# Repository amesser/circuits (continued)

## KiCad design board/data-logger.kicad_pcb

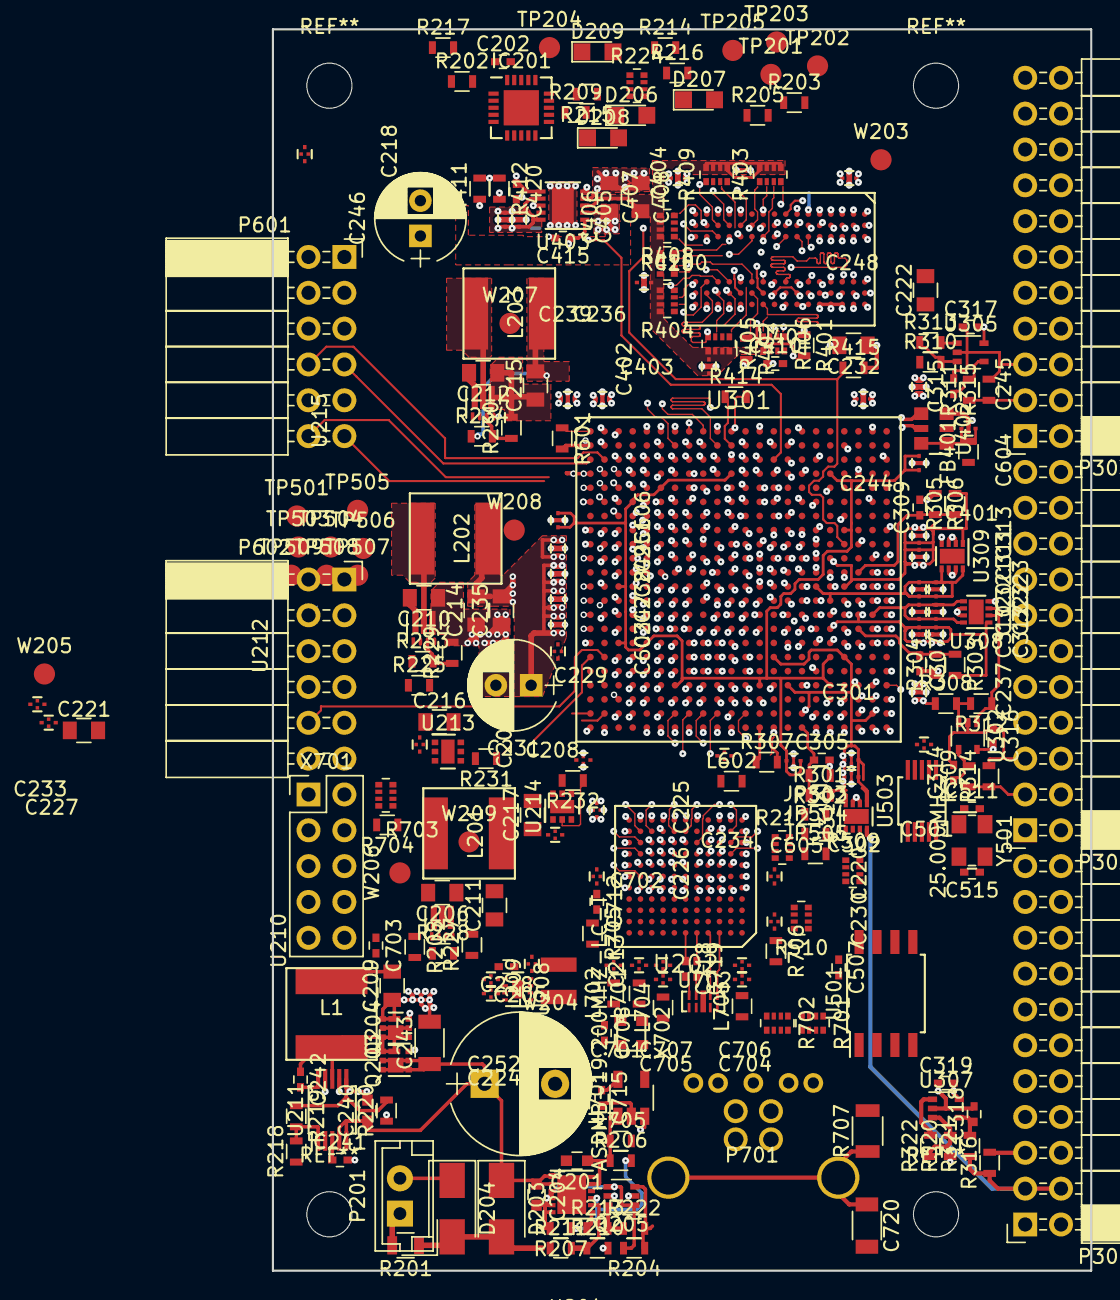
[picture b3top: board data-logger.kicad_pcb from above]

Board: 6 copper layers, 58.0 x 88.0 mm, 252 parts (1 on the bottom side), 290 nets.

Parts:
C201: 1µF/16V; C_0603
C202, C242: 0.1µF/16V; C_0402
C204, C240: 1µF/35V; C_0603
C205: 120µF/35V; CP_Radial_D10.0mm_P5.00mm
C206, C209, C210, C211, C212, C214, C215, C216, C217, C221, C222, C232, C235, C407, C408: 22µF/6.3V X5R; C_0805
C207, C208, C218, C224, C225, C227, C229, C230, C233, C234, C237, C239, C245, C252, C301, C302, C310, C311, C312, C313, C320, C321, C322, C323, C401, C405, C406, C501, C603, C604, C605, C606, C701: 1.0µF/4.0V; NFM15
C213, C220, C226, C236, C238, C244, C247, C248, C249, C250, C251, C402, C403, C404, C702, C704, C705, C706, C707: 4.3µF/2.5V; NFM15
C228: 560p; C_0402
C231, C246: 470µF/6.3V; CP_Radial_D6.3mm_P2.50mm
C241: 4.7µF/16V; C_0402
C243: 10µF/35V; C_1206
C305, C307, C309, C316, C317, C319, C410, C415, C420, C507, C703, C708, C712, C718, C719: 100n; C_0402
C314, C315, C318: 1n; C_0402
C511, C515: 10p; C_0402
C715: 1µF/16V; C_0402
C720: 100n; C_1206
D203: D_Schottky; D_SMA
D204: D_TVS; D_SMA
D206, D207, D208, D209: LED_Small; LED_0805
FB401: BLM18KG; R_0603
IC201: ATTINY2313-MU; QFN-20-1EP_4x4mm_Pitch0.5mm
JP503, JP504, JP505: R_0603
L1: 6.8µH/4.5A; Bourns_SRN6045TA
L201: 470nH/1.5A; Bourns_SRN6045TA
L202: 470nH/2.5A; Bourns_SRN6045TA
L203: 470nH/1.3A; Bourns_SRN6045TA
L209: 2.2µH/0.5A; Neosid_Inductor_SM-NE29_SMD1008
L602, L701, L702, L703, L704, L705: BLM18KG; R_0603
P201: CONN_01X02; JST_EH_B02B-EH-A_02x2.50mm_Straight
P301, P302, P303: CONN_02X11; Socket_Strip_Angled_2x11_Pitch2.54mm
P601, P602: CONN_02X06; Socket_Strip_Angled_2x06_Pitch2.54mm
P701: USB_B_3; Amphenol_GSB3211XXXWEU
Q203, Q204: CSD17313Q2; Texas_Instruments_WSON-6_2x2mm-Q2
Q205: FDG1024NZ; SOT-363_SC-70-6
R201: 0.1R; R_0805
R202, R206, R207, R208, R209, R210, R219, R220: 11k; R_0603
R203, R205, R214, R216, R234: 111k; R_0603
R204, R228: 348k; R_0603
R211: 120k n.p.; R_0603
R212, R510, R701, R702, R703: 10k; R_Array_Convex_4x0402
R213: 12.7k; R_0603
R215, R227, R229, R230: 162k; R_0603
R217, R308, R309, R310, R311, R320, R321, R401, R415: 4k7; R_0603
R218, R222: 35.7k; R_0603
R224: 470; R_Array_Convex_4x0402
R225, R312, R313, R314, R315, R316, R322: 100k; R_0603
R231: 44.2k; R_0603
R232: 21k; R_0603
R233: 60.4k; R_0603
R301, R302, R303, R304, R305, R306: 470R; R_0603
R307, R704: 100R; R_0603
R402, R414: 240; R_0603
R403, R404, R405, R406, R408, R409, R410: 51R; R_Array_Convex_4x0402
R411, R412: 10k; R_0603
R509: 1k; R_Array_Convex_4x0402
R601: 2.00k / 1%; R_0603
R705: 6.04k / 1%; R_0603
R706: 200 / 1%; R_0603
R707: 1M; R_1206
TP201, TP202, TP203, TP204, TP205, TP501, TP502, TP503, TP504, TP505, TP506, TP507, TP508, TP509: TEST; Measurement_Point_Round-SMD-Pad_Small
U202: CYUSB3012-BZXC; BGA_121_Pitch0.8
U204: NCP373MU13TXG; LLGA-12-EP_3x3mm_Pitch0.5mm
U208: MIC23050-4YML; Micrel_MLF-8_2x2mm_Pitch0.5mm
U210, U212, U215: TLV62085; Texas_Instruments-VSON-HR-7
U211: TPS53015; MSOP-10_3x3mm_Pitch0.5mm
U213, U214: NCP380; DFN-6-EP_2x2mm_Pitch0.65mm
U301: 5CEFA2F23; BGA_484_Pitch1.0
U302, U305, U307: TS881ICT; SOT-353_SC-70-5
U308, U309, U310: SiP32413; DFN-8-1EP_2x2mm_Pitch0.5mm
U401: IS43TR16256LA; BGA-96_Pitch0.8mm
U402: DSC1103CI5-100.0000; Discera_DSC11xxC_3.2x2.5mm
U403: NCP51200; DFN-10-1EP_3x3mm_Pitch0.5mm
U501: 25LC_EEPROM; SOIJ-8_5.3x5.3mm_Pitch1.27mm
U503: SI5351A-B-GT; MSOP-10_3x3mm_Pitch0.5mm
U701: NCP361SNT1G; TSOT-23-5
U702: SP3010-04UTG; SP3010
W203, W204, W205, W206, W207, W208, W209: TEST_1P; Measurement_Point_Round-SMD-Pad_Small
X701: CONN_DEBUG_MCNET; Pin_Header_Straight_2x05_Pitch2.54mm
X702: ASDMB-19.200MHZ-LC-T; Abracon_ASDMB
Y501: 25.000MHz; Crystal_SMD_3.2x2.5mm

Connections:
/Cyclone V DDR3 RAM/FPGA_CLK10_N: U301.H15, U402.4
/Cyclone V DDR3 RAM/FPGA_CLK10_P: U301.H16, U402.5
/Cyclone V DDR3 RAM/FPGA_DDR3_A0: R410.4, U301.L7, U401.N3
/Cyclone V DDR3 RAM/FPGA_DDR3_A1: R404.2, U301.K7, U401.P7
/Cyclone V DDR3 RAM/FPGA_DDR3_A2: R408.1, U301.H8, U401.P3
/Cyclone V DDR3 RAM/FPGA_DDR3_A3: R409.3, U301.G8, U401.N2
/Cyclone V DDR3 RAM/FPGA_DDR3_A4: R406.3, U301.J7, U401.P8
/Cyclone V DDR3 RAM/FPGA_DDR3_A5: R409.2, U301.J8, U401.P2
/Cyclone V DDR3 RAM/FPGA_DDR3_A6: R406.4, U301.A10, U401.R8
/Cyclone V DDR3 RAM/FPGA_DDR3_A7: R409.1, U301.A9, U401.R2
/Cyclone V DDR3 RAM/FPGA_DDR3_A8: R405.3, U301.A8, U401.T8
/Cyclone V DDR3 RAM/FPGA_DDR3_A9: R408.2, U301.A7, U401.R3
/Cyclone V DDR3 RAM/FPGA_DDR3_A10: R404.4, U301.C6, U401.L7
/Cyclone V DDR3 RAM/FPGA_DDR3_A11: R405.4, U301.D6, U401.R7
/Cyclone V DDR3 RAM/FPGA_DDR3_A12: R404.3, U301.D7, U401.N7
/Cyclone V DDR3 RAM/FPGA_DDR3_A13: R408.3, U301.C8, U401.T3
/Cyclone V DDR3 RAM/FPGA_DDR3_A14: R404.1, U301.G6, U401.T7
/Cyclone V DDR3 RAM/FPGA_DDR3_A15: R406.2, U301.H6, U401.M7
/Cyclone V DDR3 RAM/FPGA_DDR3_BA0: R409.4, U301.A5, U401.M2
/Cyclone V DDR3 RAM/FPGA_DDR3_BA1: R405.2, U301.B10, U401.N8
/Cyclone V DDR3 RAM/FPGA_DDR3_BA2: R408.4, U301.C9, U401.M3
/Cyclone V DDR3 RAM/FPGA_DDR3_CKE: R401.1, R406.1, U301.F14, U401.K9
/Cyclone V DDR3 RAM/FPGA_DDR3_CK_N: R410.1, U301.H9, U401.K7
/Cyclone V DDR3 RAM/FPGA_DDR3_CK_P: R410.2, U301.J9, U401.J7
/Cyclone V DDR3 RAM/FPGA_DDR3_D0: U301.E12, U401.F2
/Cyclone V DDR3 RAM/FPGA_DDR3_D1: U301.D12, U401.H8
/Cyclone V DDR3 RAM/FPGA_DDR3_D2: U301.C11, U401.H3
/Cyclone V DDR3 RAM/FPGA_DDR3_D3: U301.K9, U401.F8
/Cyclone V DDR3 RAM/FPGA_DDR3_D4: U301.C13, U401.H7
/Cyclone V DDR3 RAM/FPGA_DDR3_D5: U301.D13, U401.F7
/Cyclone V DDR3 RAM/FPGA_DDR3_D6: U301.B12, U401.G2
/Cyclone V DDR3 RAM/FPGA_DDR3_D7: U301.F12, U401.E3
/Cyclone V DDR3 RAM/FPGA_DDR3_D8: U301.F13, U401.C2
/Cyclone V DDR3 RAM/FPGA_DDR3_D9: U301.E14, U401.A2
/Cyclone V DDR3 RAM/FPGA_DDR3_D10: U301.J11, U401.C8
/Cyclone V DDR3 RAM/FPGA_DDR3_D11: U301.A13, U401.D7
/Cyclone V DDR3 RAM/FPGA_DDR3_D12: U301.B15, U401.A7
/Cyclone V DDR3 RAM/FPGA_DDR3_D13: U301.C15, U401.C3
/Cyclone V DDR3 RAM/FPGA_DDR3_D14: U301.G15, U401.B8
/Cyclone V DDR3 RAM/FPGA_DDR3_D15: U301.K16, U401.A3
/Cyclone V DDR3 RAM/FPGA_DDR3_DM0: U301.G11, U401.E7
/Cyclone V DDR3 RAM/FPGA_DDR3_DM1: U301.J17, U401.D3
/Cyclone V DDR3 RAM/FPGA_DDR3_DQS0_N: U301.G12, U401.G3
/Cyclone V DDR3 RAM/FPGA_DDR3_DQS0_P: U301.H11, U401.F3
/Cyclone V DDR3 RAM/FPGA_DDR3_DQS1_N: U301.J13, U401.B7
/Cyclone V DDR3 RAM/FPGA_DDR3_DQS1_P: U301.H14, U401.C7
/Cyclone V DDR3 RAM/FPGA_DDR3_ODT: R403.3, U301.L8, U401.K1
/Cyclone V DDR3 RAM/VREF_DDR3: C420.1, U301.C14, U401.H1, U401.M8, U403.6
/Cyclone V DDR3 RAM/VTT_DDR3: C402.1, C403.1, C404.1, C408.2, R403.5, R403.6, R403.7, R403.8, R404.5, R404.6, R404.7, R404.8, R405.5, R405.6, R405.7, R405.8, R406.5, R406.6, R406.7, R406.8, R408.5, R408.6, R408.7, R408.8, R409.5, R409.6, R409.7, R409.8, R410.5, R410.6, U403.3, U403.5
/Cyclone V DDR3 RAM/~FPGA_DDR3_CAS~: R403.2, U301.B6, U401.K3
/Cyclone V DDR3 RAM/~FPGA_DDR3_CS~: R403.1, U301.E9, U401.L2
/Cyclone V DDR3 RAM/~FPGA_DDR3_RAS~: R403.4, U301.B7, U401.J3
/Cyclone V DDR3 RAM/~FPGA_DDR3_RESET~: R415.1, U301.J19, U401.T2
/Cyclone V DDR3 RAM/~FPGA_DDR3_WE~: R410.3, U301.F7, U401.L3
/Cyclone V FX3 FIFO/FPGA_CLK0: U301.N9, U503.10
/Cyclone V FX3 FIFO/FPGA_CLK1: U301.M9, U503.9
/Cyclone V FX3 FIFO/FPGA_CONF_DONE: R510.8, TP507.1, U202.D3, U301.K6
/Cyclone V FX3 FIFO/FPGA_FX3_A0: U202.H5, U301.V9
/Cyclone V FX3 FIFO/FPGA_FX3_A1: U202.J5, U301.N8
/Cyclone V FX3 FIFO/FPGA_FX3_CLK: U202.J6, U301.AB8
/Cyclone V FX3 FIFO/FPGA_FX3_D0: U202.F10, U301.M6
/Cyclone V FX3 FIFO/FPGA_FX3_D1: U202.F9, U301.N6
/Cyclone V FX3 FIFO/FPGA_FX3_D2: U202.F7, U301.AA10
/Cyclone V FX3 FIFO/FPGA_FX3_D3: U202.G10, U301.R6
/Cyclone V FX3 FIFO/FPGA_FX3_D4: U202.G9, U301.U7
/Cyclone V FX3 FIFO/FPGA_FX3_D5: U202.F8, U301.R5
/Cyclone V FX3 FIFO/FPGA_FX3_D6: U202.H10, U301.U6
/Cyclone V FX3 FIFO/FPGA_FX3_D7: U202.H9, U301.T8
/Cyclone V FX3 FIFO/FPGA_FX3_D8: U202.J10, U301.T7
/Cyclone V FX3 FIFO/FPGA_FX3_D9: U202.J9, U301.P7
/Cyclone V FX3 FIFO/FPGA_FX3_D10: U202.K11, U301.P6
/Cyclone V FX3 FIFO/FPGA_FX3_D11: U202.L10, U301.AB5
/Cyclone V FX3 FIFO/FPGA_FX3_D12: U202.K10, U301.V6
/Cyclone V FX3 FIFO/FPGA_FX3_D13: U202.K9, U301.AB6
/Cyclone V FX3 FIFO/FPGA_FX3_D14: U202.J8, U301.R7
/Cyclone V FX3 FIFO/FPGA_FX3_D15: U202.G8, U301.M7
/Cyclone V FX3 FIFO/FPGA_FX3_D16: U202.K2, U301.V10
/Cyclone V FX3 FIFO/FPGA_FX3_D17: U202.J4, U301.AB10
/Cyclone V FX3 FIFO/FPGA_FX3_D18: U202.K1, U301.U12
/Cyclone V FX3 FIFO/FPGA_FX3_D19: U202.J2, U301.U10
/Cyclone V FX3 FIFO/FPGA_FX3_D20: U202.J3, U301.AA12
/Cyclone V FX3 FIFO/FPGA_FX3_D21: U202.J1, U301.U11
/Cyclone V FX3 FIFO/FPGA_FX3_D22: U202.H2, U301.R12
/Cyclone V FX3 FIFO/FPGA_FX3_D23: U202.H3, U301.AB11
/Cyclone V FX3 FIFO/FPGA_FX3_D24: U202.F4, U301.T9
/Cyclone V FX3 FIFO/FPGA_FX3_D25: U202.G2, U301.R11
/Cyclone V FX3 FIFO/FPGA_FX3_D26: U202.G3, U301.Y11
/Cyclone V FX3 FIFO/FPGA_FX3_D27: U202.F3, U301.M8
/Cyclone V FX3 FIFO/FPGA_FX3_D28: U202.F5, U301.Y10
/Cyclone V FX3 FIFO/FPGA_FX3_D29: U202.E1, U301.T10
/Cyclone V FX3 FIFO/FPGA_FX3_D30: U202.E5, U301.R10
/Cyclone V FX3 FIFO/FPGA_FX3_D31: U202.E4, U301.P12
/Cyclone V FX3 FIFO/FPGA_FX3_FLAGA: U202.G7, U301.W9
/Cyclone V FX3 FIFO/FPGA_FX3_FLAGB: U202.G6, U301.AA9
/Cyclone V FX3 FIFO/FPGA_FX3_FLAGC: U202.K6, U301.Y9
/Cyclone V FX3 FIFO/FPGA_FX3_FLAGD: U202.G5, U301.R9
/Cyclone V FX3 FIFO/FPGA_FX3_PKTEND: U202.H8, U301.AA8
/Cyclone V FX3 FIFO/JTAG_FPGA_TCK: R509.6, TP503.1, U301.V5
/Cyclone V FX3 FIFO/JTAG_FPGA_TDI: R509.1, TP504.1, U301.W5
/Cyclone V FX3 FIFO/JTAG_FPGA_TDO: TP501.1, U301.M5
/Cyclone V FX3 FIFO/JTAG_FPGA_TMS: R509.2, TP502.1, U301.P5
/Cyclone V FX3 FIFO/PMODE0: R212.2, U202.G4
/Cyclone V FX3 FIFO/PMODE1: R212.3, U202.H4
/Cyclone V FX3 FIFO/PMODE2: R212.4, U202.L4
/Cyclone V FX3 FIFO/~FPGA_CONFIG~: R510.5, TP505.1, U202.D1, U301.A4
/Cyclone V FX3 FIFO/~FPGA_FX3_INT~: U202.L8, U301.AA7
/Cyclone V FX3 FIFO/~FPGA_FX3_SLCS~: U202.K8, U301.W8
/Cyclone V FX3 FIFO/~FPGA_FX3_SLOE~: U202.J7, U301.U8
/Cyclone V FX3 FIFO/~FPGA_FX3_SLRD~: U202.H7, U301.P8
/Cyclone V FX3 FIFO/~FPGA_FX3_SLWR~: U202.K7, U301.AB7
/Cyclone V FX3 FIFO/~FPGA_STATUS~: R510.6, TP506.1, U202.D2, U301.H5
/Cyclone V Power/EXT_IO0: P601.5, U301.C1
/Cyclone V Power/EXT_IO1: P601.6, U301.C2
/Cyclone V Power/EXT_IO2: P601.7, U301.E2
/Cyclone V Power/EXT_IO3: P601.8, U301.D3
/Cyclone V Power/EXT_IO4: P601.9, U301.G1
/Cyclone V Power/EXT_IO5: P601.10, U301.G2
/Cyclone V Power/EXT_IO6: P601.11, U301.L1
/Cyclone V Power/EXT_IO7: P601.12, U301.L2
/Cyclone V Power/EXT_IO8: P602.5, U301.N1
/Cyclone V Power/EXT_IO9: P602.6, U301.N2
/Cyclone V Power/EXT_IO10: P602.7, U301.U1
/Cyclone V Power/EXT_IO11: P602.8, U301.U2
/Cyclone V Power/EXT_IO12: P602.9, U301.W2
/Cyclone V Power/EXT_IO13: P602.10, U301.Y3
/Cyclone V Power/EXT_IO14: P602.11, U301.AA1
/Cyclone V Power/EXT_IO15: P602.12, U301.AA2
/Cyclone V User IO/IO_A0_N: P301.8, U301.AA17
/Cyclone V User IO/IO_A0_P: P301.7, U301.AA18
/Cyclone V User IO/IO_A1_N: P301.10, U301.AA19
/Cyclone V User IO/IO_A1_P: P301.9, U301.AA20
/Cyclone V User IO/IO_A2_N: P301.12, U301.AB22
/Cyclone V User IO/IO_A2_P: P301.11, U301.AA22
/Cyclone V User IO/IO_A3_N: P301.14, U301.AB17
/Cyclone V User IO/IO_A3_P: P301.13, U301.AB18
/Cyclone V User IO/IO_A4_N: P301.16, U301.AB20
/Cyclone V User IO/IO_A4_P: P301.15, U301.AB21
/Cyclone V User IO/IO_A5_N: P301.18, U301.Y20
/Cyclone V User IO/IO_A5_P: P301.17, U301.Y19
/Cyclone V User IO/IO_A6_N: P301.20, U301.Y21
/Cyclone V User IO/IO_A6_P: P301.19, U301.W21
/Cyclone V User IO/IO_A7_N: P301.22, U301.Y22
/Cyclone V User IO/IO_A7_P: P301.21, U301.W22
/Cyclone V User IO/IO_B0_N: P302.8, U301.R15
/Cyclone V User IO/IO_B0_P: P302.7, U301.T15
/Cyclone V User IO/IO_B1_N: P302.10, U301.R17
/Cyclone V User IO/IO_B1_P: P302.9, U301.R16
/Cyclone V User IO/IO_B2_N: P302.12, U301.T20
/Cyclone V User IO/IO_B2_P: P302.11, U301.T19
/Cyclone V User IO/IO_B3_N: P302.14, U301.R22
/Cyclone V User IO/IO_B3_P: P302.13, U301.T22
/Cyclone V User IO/IO_B4_N: P302.16, U301.T17
/Cyclone V User IO/IO_B4_P: P302.15, U301.T18
/Cyclone V User IO/IO_B5_N: P302.18, U301.P22
/Cyclone V User IO/IO_B5_P: P302.17, U301.R21
/Cyclone V User IO/IO_B6_N: P302.20, U301.P18
/Cyclone V User IO/IO_B6_P: P302.19, U301.P19
/Cyclone V User IO/IO_B7_N: P302.22, U301.P17
/Cyclone V User IO/IO_B7_P: P302.21, U301.P16
/Cyclone V User IO/IO_C0_N: P303.8, U301.M21
/Cyclone V User IO/IO_C0_P: P303.7, U301.M20
/Cyclone V User IO/IO_C1_N: P303.10, U301.L22
/Cyclone V User IO/IO_C1_P: P303.9, U301.M22
/Cyclone V User IO/IO_C2_N: P303.12, U301.K22
/Cyclone V User IO/IO_C2_P: P303.11, U301.K21
/Cyclone V User IO/IO_C3_N: P303.14, U301.N21
/Cyclone V User IO/IO_C3_P: P303.13, U301.N20
/Cyclone V User IO/IO_C4_N: P303.16, U301.M16
/Cyclone V User IO/IO_C4_P: P303.15, U301.N16
/Cyclone V User IO/IO_C5_N: P303.18, U301.M18
/Cyclone V User IO/IO_C5_P: P303.17, U301.N19
/Cyclone V User IO/IO_C6_N: P303.20, U301.L18
/Cyclone V User IO/IO_C6_P: P303.19, U301.L19
/Cyclone V User IO/IO_C7_N: P303.22, U301.L17
/Cyclone V User IO/IO_C7_P: P303.21, U301.K17
/Cyclone V User IO/VCCIO_IO_A: C301.1, C302.1, R301.2, U301.AA16, U301.AA21, U301.U14, U301.U19, U301.W15, U301.W20, U310.5, U310.8
/Cyclone V User IO/VCCIO_IO_A_IN: P301.3, P301.4, R316.1, R321.1, U310.4
/Cyclone V User IO/VCCIO_IO_B: C310.1, C312.1, P302.3, P302.4, R303.2, R309.1, R314.1, U301.P20, U301.R18, U308.1
/Cyclone V User IO/VCCIO_IO_C: C311.1, C313.1, P303.3, P303.4, R305.2, R311.1, R315.1, U301.K18, U301.M19, U309.1
/Cyclone V User IO/VREF_B4: C305.1, R301.1, R302.2, U301.AB16
/Cyclone V User IO/VREF_B5A: C307.1, R303.1, R304.2, U301.R20
/Cyclone V User IO/VREF_B5B: C309.1, R305.1, R306.2, U301.L20
/FX3 Peripherals/JTAG_FX3_TCK: R703.1, U202.F6, X701.3
/FX3 Peripherals/JTAG_FX3_TDI: R702.2, U202.E7, X701.6
/FX3 Peripherals/JTAG_FX3_TDO: U202.C10, X701.2
/FX3 Peripherals/JTAG_FX3_TMS: R702.4, U202.E8, X701.5
/FX3 Peripherals/USB_D_N: P701.2, U202.A10
/FX3 Peripherals/USB_D_P: P701.3, U202.A9
/FX3 Peripherals/USB_SS_RX_N: P701.9, U202.A3, U702.1, U702.10
/FX3 Peripherals/USB_SS_RX_P: P701.8, U202.A4, U702.2, U702.9
/FX3 Peripherals/USB_SS_TX_N: P701.5, U702.6
/FX3 Peripherals/USB_SS_TX_P: C719.2, P701.6, U702.4, U702.7
/FX3 Peripherals/~FX3_SPI_FLASHCS~: R701.3, U202.C1, U501.1
/FX3 Peripherals/~JTAG_FX3_TRST~: R702.3, U202.B11, X701.4
/FX3 USB & Power Supply/FPGA_PG: IC201.14, U213.4, U214.4, U215.2
/FX3 USB & Power Supply/FPGA_PWREN: IC201.13, R214.2, U212.1
/FX3 USB & Power Supply/PG_1V10: R225.1, U212.2, U213.3, U214.3, U215.1
/FX3 USB & Power Supply/VCC_IN: C204.1, C205.1, C240.1, C243.1, D203.1, Q203.1, U204.1, U204.2, U211.4, U211.5
/FX3 USB & Power Supply/~ATTINY_RESET~: IC201.19, R202.1, TP202.1, U210.2
FPGA_CLK2: U301.W16, U503.6
FX3_I2C_SCL: IC201.17, R701.2, TP203.1, U202.D9, U301.U21, U503.4
FX3_I2C_SDA: IC201.15, R701.4, TP204.1, U202.D10, U301.U20, U503.5
FX3_SPI_CLK: R701.1, U202.D4, U301.V3, U501.6
FX3_SPI_MISO: U202.C2, U501.2
FX3_SPI_MOSI: U202.D5, U301.AB4, U501.5
GND: C201.2, C202.1, C204.2, C205.2, C206.1, C207.2, C208.2, C209.1, C210.1, C211.1, C212.1, C213.2, C214.1, C215.1, C216.1, C217.1, C218.2, C220.2, C221.1, C222.1, C224.2, C225.2, C226.2, C227.2, C229.2, C230.2, C231.2, C232.1, C233.2, C234.2, C235.1, C236.2, C237.2, C238.2, C239.2, C240.2, C241.2, C243.2, C244.2, C245.2, C246.2, C247.2, C248.2, C249.2, C250.2, C251.2, C252.2, C301.2, C302.2, C305.2, C307.2, C309.2, C310.2, C311.2, C312.2, C313.2, C314.2, C315.2, C316.1, C317.1, C318.2, C319.1, C320.2, C321.2, C322.2, C323.2, C401.2, C402.2, C403.2, C404.2, C405.2, C406.2, C407.1, C408.1, C410.1, C415.2, C420.2, C501.2, C507.2, C511.2, C515.2, C603.2, C604.2, C605.2, C606.2, C701.2, C702.2, C703.2, C704.2, C705.2, C706.2, C707.2, C708.2, C712.2, C715.2, C720.2, D204.1, IC201.8, IC201.21, JP505.1, JP505.2, P201.2, P301.5, P301.6, P302.5, P302.6, P303.5, P303.6, P601.3, P601.4, P602.3, P602.4, P701.4, P701.7, Q204.3, Q205.1, Q205.4, R203.2, R204.2, R205.1, R207.2, R210.2, R212.5, R214.1, R215.1, R216.1, R219.1, R220.2, R227.2, R229.2, R230.2, R231.1, R232.1, R302.1, R304.1, R306.1, R307.2, R314.2, R315.2, R316.2, R401.2, R402.2, R412.2, R414.2, R415.2, R509.3, R601.2, R705.2, R706.2, R707.2, TP205.1, TP509.1, U202.A1, U202.A8, U202.B2, U202.B4, U202.B7, U202.B8, U202.B9, U202.D8, U202.E2, U202.G1, U202.G11, U202.K3, U202.K4, U202.L1, U202.L2, U202.L3, U202.L6, U202.L11, U204.3, U204.4, U204.5, U204.6, U208.6, U208.8, U208.EP, U210.5, U211.6, U212.5, U213.2, U213.EP, U214.2, U214.EP, U215.5, U301.A2, U301.A11, U301.A21, U301.AA3, U301.AA4, U301.AA6, U301.AA11, U301.AB1, U301.AB2, U301.AB9, U301.AB14, U301.AB19, U301.B1, U301.B2, U301.B8, U301.B9, U301.B14, U301.C3, U301.C4, U301.C5, U301.C17, U301.D1, U301.D2, U301.D5, U301.D10, U301.D20, U301.E3, U301.E4, U301.E5, U301.E13, U301.F1, U301.F2, U301.F5, U301.F6, U301.F16, U301.F17, U301.G3, U301.G4, U301.G9, U301.G19, U301.H1, U301.H2, U301.H3, U301.H4, U301.H7, U301.H12, U301.H22, U301.J3, U301.J5, U301.J6, U301.J15, U301.J20, U301.K1, U301.K2, U301.K4, U301.K8, U301.K10, U301.K12, U301.K14, U301.L3, U301.L5, U301.L11, U301.L13, U301.L15, U301.L21, U301.M1, U301.M2, U301.M4, U301.M10, U301.M12, U301.M14, U301.N3, U301.N5, U301.N7, U301.N11, U301.N13, U301.N15, U301.N17, U301.N22, U301.P1, U301.P2, U301.P4, U301.P10, U301.R3, U301.R13, U301.T1, U301.T2, U301.T16, U301.T21, U301.U3, U301.U4, U301.U5, U301.U9, U301.V1, U301.V2, U301.V4, U301.V7, U301.V12, U301.V17, U301.V22, U301.W1, U301.W3, U301.W4, U301.Y1, U301.Y2, U301.Y5, U301.Y7, U301.Y12, U301.Y18, U302.2, U305.2, U307.2, U308.6, U308.7, U309.6, U309.7, U310.6, U310.7, U401.A9, U401.B1, U401.B3, U401.B9, U401.D1, U401.D8, U401.E1, U401.E2, U401.E8, U401.F9, U401.G1, U401.G8, U401.G9, U401.J2, U401.J8, U401.M1, U401.M9, U401.P1, U401.P9, U401.T1, U401.T9, U402.3, U403.4, U403.8, U403.EP, U501.4, U503.8, U701.2, U701.3, U702.3, U702.8, X701.7, X702.2, Y501.2, Y501.4
unnamed: C228.2, U208.5
unnamed: C241.1, U211.3
unnamed: C242.1, L1.1, Q203.3, Q204.1, U211.8
unnamed: C242.2, U211.10
unnamed: C314.1, R309.2, U302.4
unnamed: C315.1, R311.2, U305.4
unnamed: C318.1, R321.2, U307.4
unnamed: C401.1, FB401.2, U402.1, U402.6
unnamed: C410.2, R410.7, R410.8
unnamed: C415.1, R411.2, R412.1, U403.1
unnamed: C511.1, U503.2, Y501.1
unnamed: C515.1, U503.3, Y501.3
unnamed: C603.1, C604.1, C605.1, C606.1, L602.2, U301.D11, U301.D18, U301.E6, U301.F4, U301.H19, U301.M3, U301.T3, U301.T5, U301.U18, U301.W7, U301.W13, U301.W18
unnamed: C701.1, L702.2, U202.B6
unnamed: C702.1, L701.2, U202.A7
unnamed: C703.1, R704.2, X701.9
unnamed: C704.1, C706.1, L703.2, U202.A2
unnamed: C705.1, C707.1, L704.2, U202.B5
unnamed: C715.1, U202.E11, U701.5
unnamed: C718.1, U202.A6
unnamed: C718.2, U702.5
unnamed: C719.1, U202.A5
unnamed: C720.1, P701.S, R707.1
unnamed: D203.2, D204.2, R201.1, R211.1
unnamed: D206.1, IC201.9
unnamed: D206.2, R224.1
unnamed: D207.1, IC201.7
unnamed: D207.2, R224.2
unnamed: D208.1, IC201.6
unnamed: D208.2, R224.3
unnamed: D209.1, IC201.5
unnamed: D209.2, R224.4
unnamed: IC201.1, Q205.5, R205.2
unnamed: IC201.2, R217.1
unnamed: IC201.4, U204.10
unnamed: IC201.11, R209.1, R215.2
unnamed: IC201.16, TP201.1
unnamed: IC201.20, Q205.2, R203.1
unnamed: JP504.2, R212.6
unnamed: L201.1, U210.6
unnamed: L202.1, U212.6
unnamed: L203.1, U215.6
unnamed: L209.1, U208.1
unnamed: L705.2, P701.1
unnamed: P201.1, R201.2
unnamed: Q203.2, U211.9
unnamed: Q204.2, R220.1, U211.7
unnamed: Q205.3, R204.1, R222.2
unnamed: Q205.6, R213.2, R222.1
unnamed: R206.2, R207.1, U204.9
unnamed: R208.1, U208.2, U210.1, U211.2
unnamed: R210.1, R211.2, U204.8
unnamed: R213.1, U204.7
unnamed: R218.2, R219.2, U211.1
unnamed: R227.1, R228.2, U210.3
unnamed: R229.1, R233.2, U212.3
unnamed: R230.1, R234.2, U215.3
unnamed: R231.2, U213.5
unnamed: R232.2, U214.5
unnamed: R307.1, U301.AB13
unnamed: R308.2, R312.2, U302.3
unnamed: R310.2, R313.1, U305.3
unnamed: R312.1, U302.1, U308.2, U308.3
unnamed: R313.2, U305.1, U309.2, U309.3
unnamed: R320.2, R322.2, U307.3
unnamed: R322.1, U307.1, U310.2, U310.3
unnamed: R402.1, U401.L8
unnamed: R414.1, U301.B11
unnamed: R601.1, U301.A1
unnamed: R705.1, U202.C8
unnamed: R706.1, U202.B3
unnamed: U202.D7, X702.3
VCCPD_B5A: C320.1, C322.1, U301.P21, U308.5, U308.8
VCCPD_B5B: C321.1, C323.1, U301.M17, U301.N18, U309.5, U309.8
VCC_1V10_FPGA: C214.2, C231.1, C235.2, C238.1, C247.1, C249.1, C251.1, L202.2, R233.1, U212.4, U301.J4, U301.J10, U301.J12, U301.J14, U301.J16, U301.K3, U301.K5, U301.K11, U301.K13, U301.K15, U301.L4, U301.L10, U301.L12, U301.L14, U301.L16, U301.M11, U301.M13, U301.M15, U301.N4, U301.N10, U301.N12, U301.N14, U301.P3, U301.P11, U301.P13, U301.P15, W208.1
VCC_1V20: C213.1, C220.1, C226.1, C228.1, L209.2, L701.1, L703.1, L704.1, R209.2, U202.B10, U202.C3, U202.E9, U202.F11, U202.H1, U202.J11, U202.L5, U202.L7, U208.4, W204.1
VCC_1V35_FPGA: C215.2, C232.2, C236.1, C244.1, C248.1, C250.1, C407.2, L203.2, R234.1, R411.1, U215.4, U301.A6, U301.A16, U301.B19, U301.C7, U301.C12, U301.C22, U301.D15, U301.E8, U301.E18, U301.F11, U301.F21, U301.G7, U301.G14, U301.H17, U401.A1, U401.A8, U401.B2, U401.C1, U401.C9, U401.D2, U401.D9, U401.E9, U401.F1, U401.G7, U401.H2, U401.H9, U401.K2, U401.K8, U401.N1, U401.N9, U401.R1, U401.R9, U403.2, W207.1
VCC_2V50: C208.1, C211.2, C225.1, C230.1, C501.1, C507.1, C708.1, JP503.1, JP503.2, JP504.1, L201.2, L702.1, R212.7, R228.1, R701.5, R701.6, R701.7, R701.8, R702.5, R702.6, R702.7, R702.8, R703.8, R704.1, U202.B1, U202.C11, U202.E3, U202.E6, U202.F1, U202.H11, U202.L9, U210.4, U214.1, U501.3, U501.7, U501.8, U503.1, U503.7, W209.1, X702.1, X702.4
VCC_2V50_FPGA: C217.2, C222.2, C229.1, C234.1, C237.1, C239.1, C245.1, C405.1, C406.1, FB401.1, L602.1, P301.2, P302.2, P303.2, R308.1, R310.1, R320.1, R509.7, R509.8, R510.1, R510.3, R510.4, U214.6, U301.A3, U301.C10, U301.D8, U301.D14, U301.D16, U301.E11, U301.F3, U301.F8, U301.L6, U301.R8, U301.R19, U301.T6, U301.T11, U301.V8, U301.W6, U301.W10, U301.W11, U301.W12, U301.W14, U301.W17, U301.Y8, U301.Y13, U308.4, U309.4, U310.1, U403.7, U403.10, W203.1
VCC_3V30: C202.2, C206.2, C207.1, C209.2, C210.2, C212.2, C218.1, C224.1, C246.1, C252.1, C712.1, IC201.18, L1.2, R202.2, R208.2, R218.1, R224.5, R224.6, R224.7, R224.8, R225.2, U202.E10, U208.7, U210.7, U212.7, U213.1, U215.7, W206.1
VCC_3V30_FPGA: C216.2, C221.2, C227.1, C233.1, C316.2, C317.2, C319.2, P301.1, P302.1, P303.1, P601.1, P601.2, P602.1, P602.2, U213.6, U301.D4, U301.E1, U301.J1, U301.J2, U301.R1, U301.R2, U301.Y4, U302.5, U305.5, U307.5, W205.1
VCC_USB: C201.1, L705.1, R206.1, U204.11, U701.1
~FX3_SPI_FPGACS~: R702.1, U202.C4, U301.G5
~RESET~: R216.2, R217.2, U202.C5, X701.1

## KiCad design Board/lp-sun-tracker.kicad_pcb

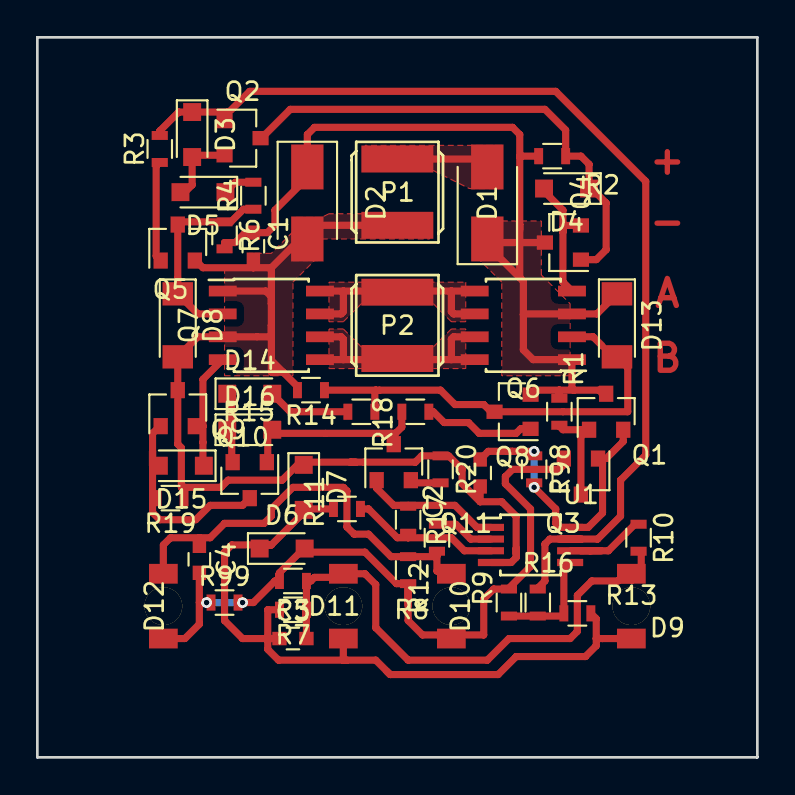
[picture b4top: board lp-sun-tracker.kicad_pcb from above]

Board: 2 copper layers, 40.0 x 40.0 mm, 56 parts (0 on the bottom side), 31 nets.

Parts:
C1, C2, C3, C4: 100n; C_0603
D1: D; D_SMA_Standard
D2: D_TVS; D_SMA_Standard
D3, D4, D5, D6, D7, D14, D15, D16: D; D_SOD-323_HandSoldering
D8, D13: 15V; D_MiniMELF_Standard
D9: E; Würth_WL_SMRW_Cylindrical_ReverseMount_1206
D10: SE; Würth_WL_SMRW_Cylindrical_ReverseMount_1206
D11: SW; Würth_WL_SMRW_Cylindrical_ReverseMount_1206
D12: W; Würth_WL_SMRW_Cylindrical_ReverseMount_1206
P1, P2: CONN_01X02; Choke_SMD_Taiyo_NRS50XX
Q1, Q2, Q3, Q4, Q5, Q11: BC847; SOT-23
Q6: IRF7304; SOIC-8_3.9x4.9mm_Pitch1.27mm
Q7: IRF7303; SOIC-8_3.9x4.9mm_Pitch1.27mm
Q8, Q9, Q10: BC857; SOT-23
R1, R10, R11, R12, R13: 100k; R_0603
R2, R3, R6, R9, R14, R18, R19, R20: 22k; R_0603
R4: 1k; R_0603
R5: 10M; R_0603
R7: n.p.; R_0603
R8: 5.1M; R_0603
R15: 1.0k; R_0603
R16, R17: 1M; R_0603
R98, R99: 0; R_0603
U1: TS882IST; MSOP-8_3x3mm_Pitch0.65mm

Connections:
/DAY_DETECT: D3.1, Q2.1, R3.1, R16.1, U1.7
/FOLLOW_SUN: Q11.1, R17.1, U1.1
/MOTOR_A: P2.1, Q6.5, Q6.6, Q7.7, Q7.8
/MOTOR_B: P2.2, Q6.7, Q6.8, Q7.5, Q7.6
/V+: C1.1, D1.1, D2.1, D13.1, Q1.3, Q4.3, Q6.1, Q6.3, Q8.2, R1.1, R2.1, R6.1
/VCC_1V5: C2.2, Q1.2, Q3.1, R98.1, R98.2, U1.8
GND: C1.2, C2.1, D2.2, D7.1, D8.2, P1.2, Q5.2, Q7.1, Q7.3, Q9.3, R14.2, R19.2, R20.1, U1.4
unnamed: C3.1, D6.1, D7.2, D9.2, D11.2, R7.2, R11.2, R13.2
unnamed: C3.2, D9.1, D11.1, R5.1, R7.1, R10.2
unnamed: C4.1, D10.2, D12.1, R8.2, R12.2
unnamed: C4.2, D6.2, D10.1, D12.2, Q3.2, R5.2, R8.1, R9.2, R99.1, R99.2
unnamed: D1.2, P1.1
unnamed: D3.2, D5.2, Q2.2
unnamed: D4.1, Q2.3, Q4.1, R2.2
unnamed: D4.2, Q4.2, Q6.4
unnamed: D5.1, R4.1
unnamed: D8.1, Q5.3, Q7.2, R4.2, R6.2
unnamed: D13.2, Q6.2, Q8.3, R14.1, R15.1
unnamed: D14.1, D16.1, Q10.2
unnamed: D14.2, R15.2
unnamed: D15.1, Q7.4, Q9.2
unnamed: D15.2, Q9.1, Q10.3, R19.1
unnamed: D16.2, Q10.1, Q11.3, R18.2
unnamed: Q1.1, Q3.3, R1.2
unnamed: Q5.1, R3.2
unnamed: Q8.1, R18.1
unnamed: Q11.2, R20.2
unnamed: R10.1, U1.6
unnamed: R11.1, R17.2, U1.3
unnamed: R12.1, U1.2
unnamed: R9.1, R13.1, R16.2, U1.5

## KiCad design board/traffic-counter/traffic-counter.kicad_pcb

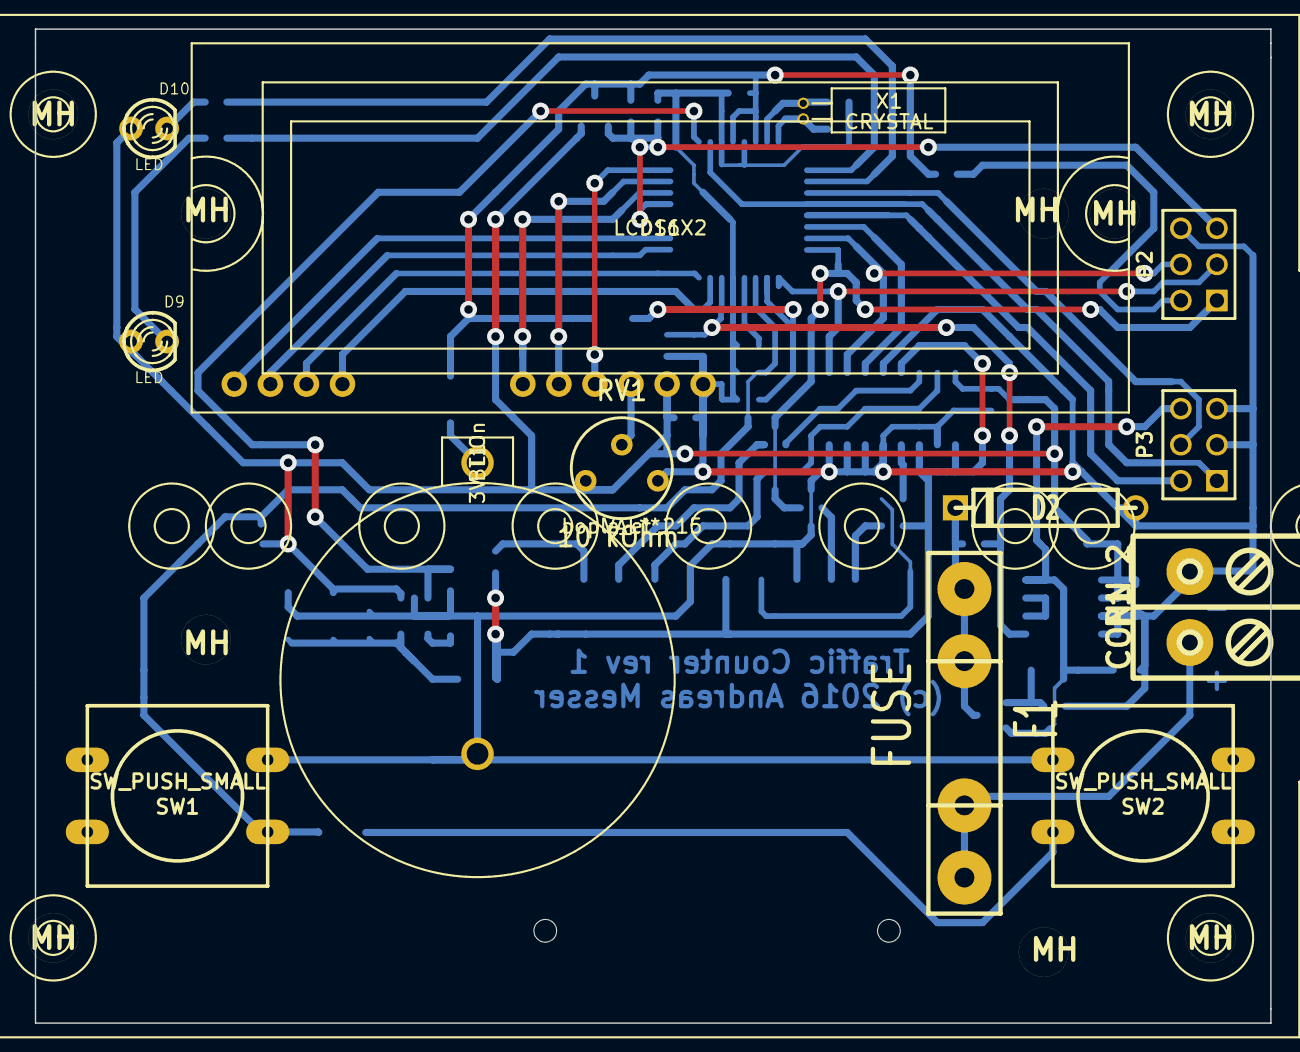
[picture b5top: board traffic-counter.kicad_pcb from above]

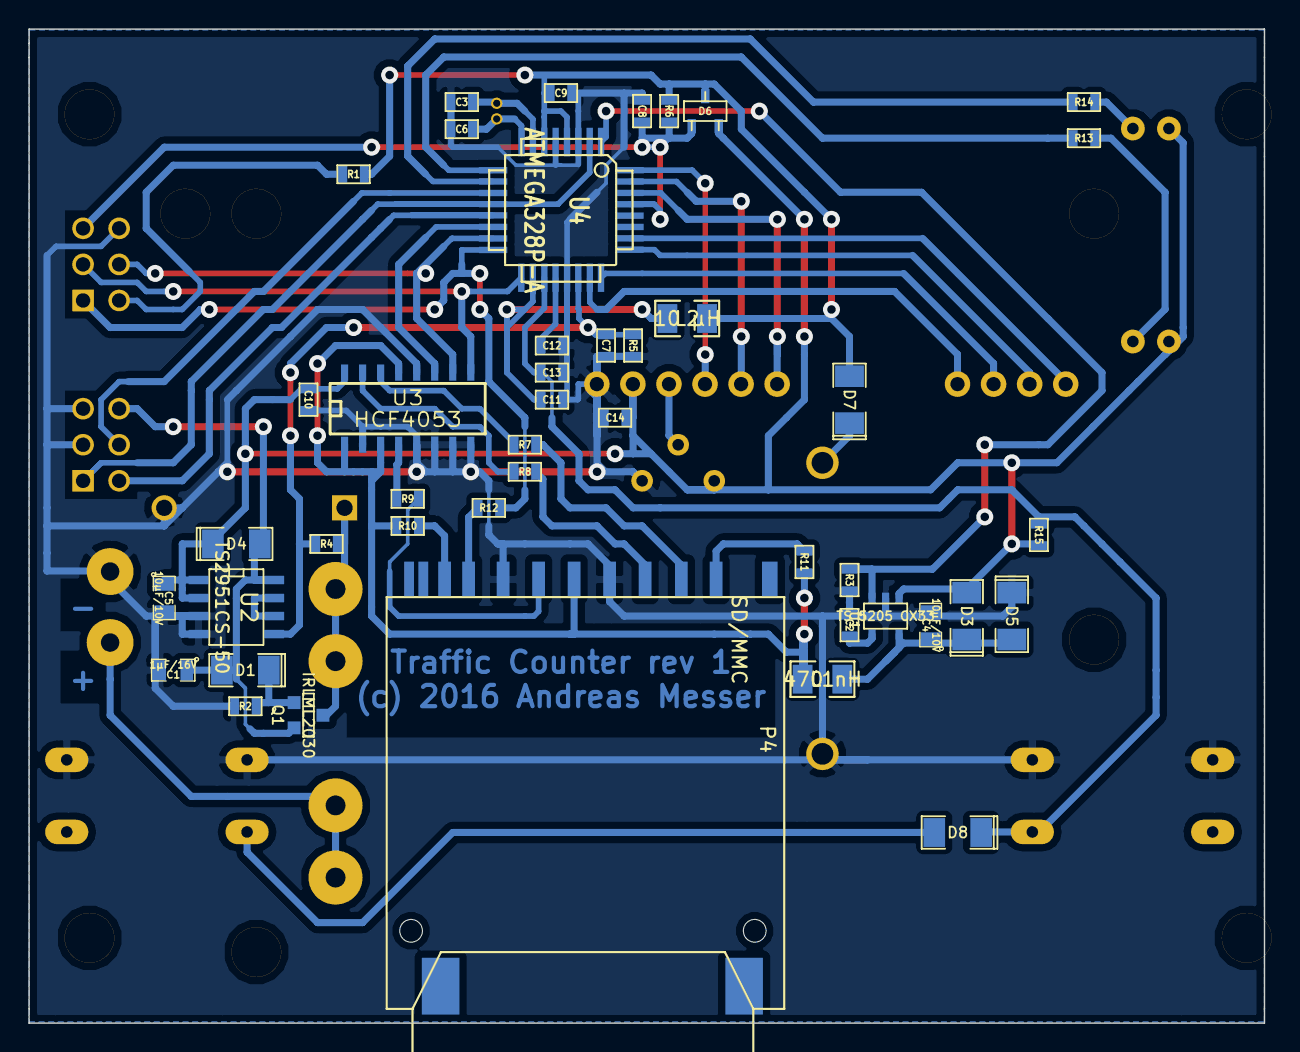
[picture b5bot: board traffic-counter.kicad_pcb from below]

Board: 2 copper layers, 87.0 x 70.0 mm, 67 parts (44 on the bottom side), 50 nets.

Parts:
BT1: 3V LiOn; keystone_electronics_106
C1: 1µF/16V; SM0805
C2, C8, C9, C10, C11, C12, C14: 100nF; SM0603
C3, C6: 22 pF; SM0603
C4, C5: 10µF/10V; SM0805
C7: 10nF; SM0603
C13: 10 nF; SM0603
D1, D5: BZV 55 5.1V; SM1206POL
D2: P6KE15CA; D5
D3, D4, D7, D8: DIODE; SM1206POL
D6: BAT54C; sot23
D9, D10: LED; LED-3MM
DS1: LCD16X2; lumex_LCM-S01602DTR_4bit
F1: FUSE; FUSE5-20
L1: 470 nH; SM1008
L2: 10 µH; SM1008
MH: MountingHole_3-5mm_RevA_Date21Jun2010
MH#2, MH#3, MH#4, MH#5, MH#6, MH#7, MH#8, MH#9: MountingHole_3-5mm_RevA_Date21Jun2010
P1: CONN_2; RIACON_007-2
P2: CONN_6; pin_array_3x2
P3: CONN_3X2; pin_array_3x2
P4: SD/MMC; yamaichi_fps_009_2409
Q1: IRLML2030; SOT23GDS
R1, R6, R15: 10 kOhm; SM0603
R2, R4: 100kOhm; SM0603
R3, R10, R11: 100 kOhm; SM0603
R5: 47kOhm; SM0603
R7, R8, R9, R12: 40 Ohm; SM0603
R13, R14: 3.3 kOhm; SM0603
RV1: 10 kOhm; RV2
SW1, SW2: SW_PUSH_SMALL; SW_PUSH-12mm
U1: TS 5205 CX33; SOT23-5
U2: TS2951CS-50; SO8E
U3: HCF4053; SO16E
U4: ATMEGA328P-A; TQFP32
X1: CRYSTAL; TC-38
bopla_et_215: VAL**; bopla_et_215

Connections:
+5V: C5.1, C10.1, C14.2, D3.2, D4.1, D6.3, D9.1, D10.1, DS1.2, R15.2, RV1.1, U1.1, U2.1, U2.2, U3.16
/#RADAR_EN: P3.4, U4.11
/#RESET: C8.1, D6.1, P2.5, R6.2, U4.29
/#SD_CS: U3.11, U4.14
/#SD_PWREN: R3.2, U1.3, U4.1
/ADC_BAT: C7.1, R4.1, R5.1, U2.5, U4.22
/ADC_KEY: C13.1, D8.1, R15.1, SW1.1, U4.19
/MISO: P2.1, R12.1, U4.16
/MOSI: P2.4, U3.10, U4.15
/RADAR_I: P3.1, U4.2, U4.12
/RADAR_Q: P3.2, U4.13
/SCK: P2.3, U3.9, U4.17
/Vbat: D2.2, F1.2, Q1.D, R4.2
/Vmicro: C9.1, D6.2, D7.2, L2.2, R1.2, R6.1, U4.4, U4.6
/Vsupply: C1.1, D1.2, D4.2, P3.6, Q1.S, U2.8
/XTAL1: C3.1, U4.7, X1.1
/XTAL2: C6.1, U4.8, X1.2
GND: BT1.2, C1.2, C2.1, C3.2, C4.2, C5.2, C6.2, C7.2, C8.2, C9.2, C10.2, C11.2, C12.2, C13.2, C14.1, D2.1, D5.1, DS1.1, P1.2, P2.6, P3.3, P3.5, P4.3, P4.6, R2.1, R3.1, R5.2, RV1.3, SW1.2, SW2.2, U1.2, U2.3, U2.4, U3.2, U3.5, U3.6, U3.7, U3.8, U3.12, U4.3, U4.5, U4.21
unnamed: P4.5, R9.2
unnamed: P4.1, R7.2
unnamed: P4.2, R8.2
unnamed: R9.1, U3.4
unnamed: P4.7, R12.2
unnamed: C4.1, D3.1, D5.2, L1.1, U1.5
unnamed: C2.2, U1.4
unnamed: P4.9, R11.2
unnamed: P4.8, R10.2
unnamed: C11.1, L2.1, U4.18
unnamed: F1.1, P1.1
unnamed: R14.1, U4.10
unnamed: R13.1, U4.9
unnamed: D10.2, R14.2
unnamed: U2.6, U2.7
unnamed: DS1.12, U4.24
unnamed: DS1.13, U4.25
unnamed: DS1.14, U4.26
unnamed: D8.2, SW2.1
unnamed: BT1.1, D7.1
unnamed: DS1.3, RV1.2
unnamed: DS1.11, U4.23
unnamed: C12.1, U4.20
unnamed: DS1.6, U4.30
unnamed: R8.1, U3.15
unnamed: R7.1, U3.14
unnamed: DS1.5, U4.31
unnamed: DS1.4, U4.32
unnamed: D9.2, R13.2
unnamed: D1.1, Q1.G, R2.2
unnamed: L1.2, P4.4, R10.1, R11.1, U3.1, U3.3, U3.13
unnamed: P2.2, R1.1
